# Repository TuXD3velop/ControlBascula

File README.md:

# ControlBascula
Controla el on-off de un motor que llena un recipiente, usando el peso de la bascula como parametro

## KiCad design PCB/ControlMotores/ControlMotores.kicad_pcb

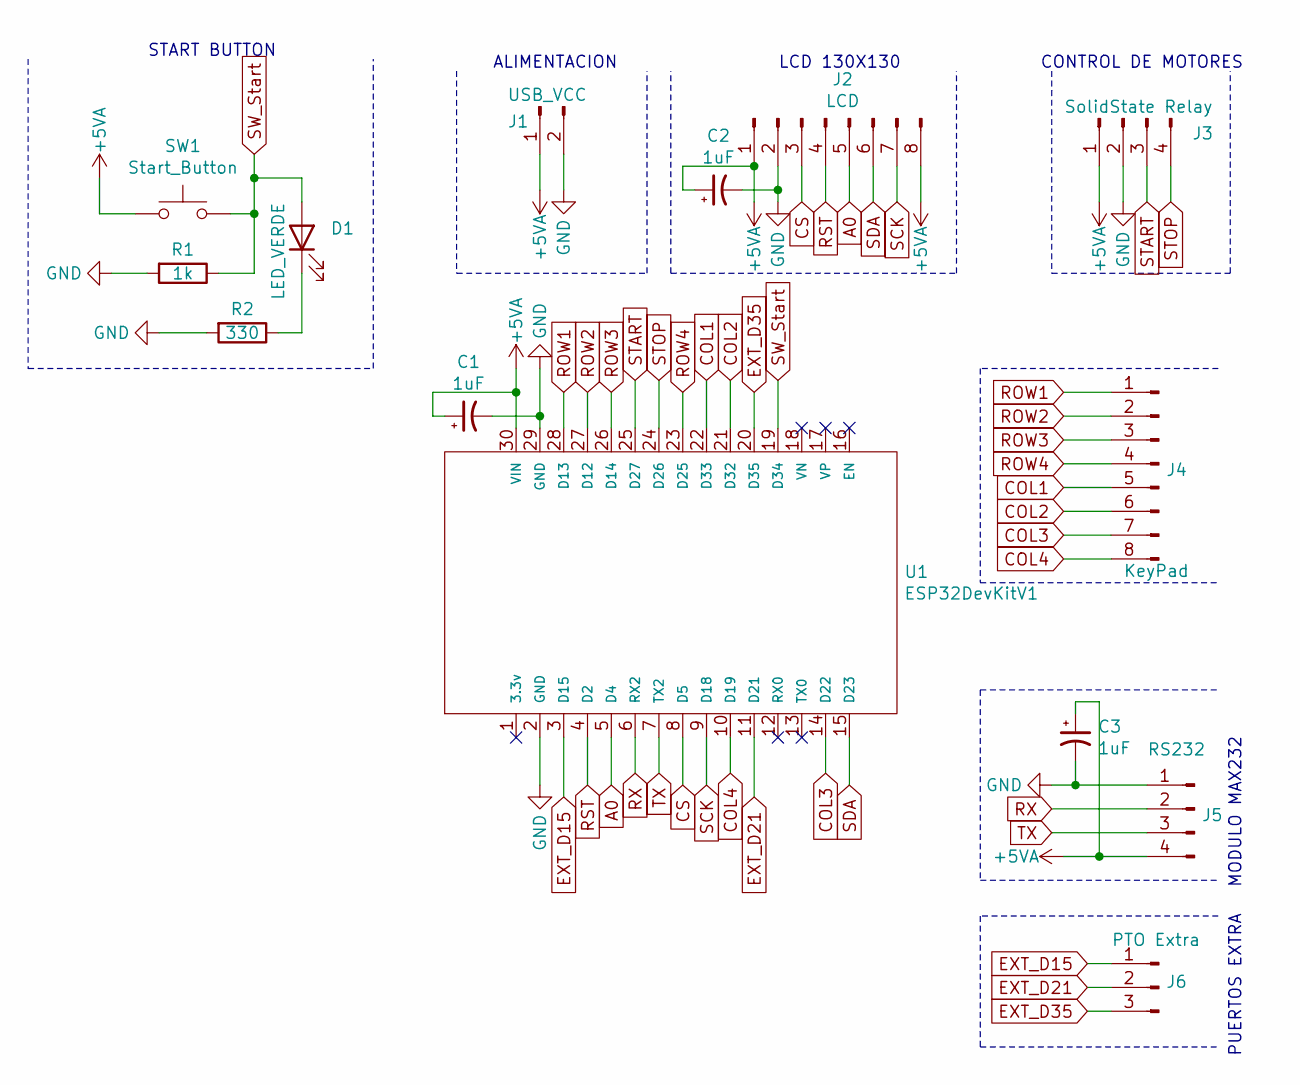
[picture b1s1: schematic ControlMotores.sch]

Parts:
C1, C2, C3: 1uF; CP_Radial_D8.0mm_P3.80mm
D1: LED_VERDE; PinHeader_1x02_P2.54mm_Vertical
J1: USB_VCC; PinHeader_1x02_P2.54mm_Horizontal
J2: LCD; PinHeader_1x08_P2.54mm_Vertical
J3: SolidState Relay; PinHeader_1x04_P2.54mm_Vertical
J4: KeyPad; PinHeader_1x08_P2.54mm_Vertical
J5: RS232; PinHeader_1x04_P2.54mm_Vertical
J6: PTO Extra; PinHeader_1x03_P2.54mm_Vertical
R1: 1k; R_Axial_DIN0204_L3.6mm_D1.6mm_P7.62mm_Horizontal
R2: 330; R_Axial_DIN0204_L3.6mm_D1.6mm_P7.62mm_Horizontal
SW1: Start_Button; TerminalBlock_bornier-2_P5.08mm
U1: ESP32DevKitV1

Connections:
+5VA: C1.1, C2.1, C3.1, J1.1, J2.1, J2.8, J3.1, J5.4, SW1.1, U1.30 (VIN)
A0: J2.5, U1.5 (D4)
COL1: J4.5, U1.22 (D33)
COL2: J4.6, U1.21 (D32)
COL3: J4.7, U1.14 (D22)
COL4: J4.8, U1.10 (D19)
CS: J2.3, U1.8 (D5)
EXT_D15: J6.1, U1.3 (D15)
EXT_D21: J6.2, U1.11 (D21)
EXT_D35: J6.3, U1.20 (D35)
GND: C1.2, C2.2, C3.2, J1.2, J2.2, J3.2, J5.1, R1.2, R2.2, U1.2 (GND), U1.29 (GND)
unnamed: D1.1 (K), R2.1
ROW1: J4.1, U1.28 (D13)
ROW2: J4.2, U1.27 (D12)
ROW3: J4.3, U1.26 (D14)
ROW4: J4.4, U1.23 (D25)
RST: J2.4, U1.4 (D2)
RX: J5.2, U1.6 (RX2)
SCK: J2.7, U1.9 (D18)
SDA: J2.6, U1.15 (D23)
START: J3.3, U1.25 (D27)
STOP: J3.4, U1.24 (D26)
SW_Start: D1.2 (A), R1.1, SW1.2, U1.19 (D34)
TX: J5.3, U1.7 (TX2)

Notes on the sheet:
ALIMENTACION
LCD 130X130
CONTROL DE MOTORES
MODULO MAX232
START BUTTON
PUERTOS EXTRA

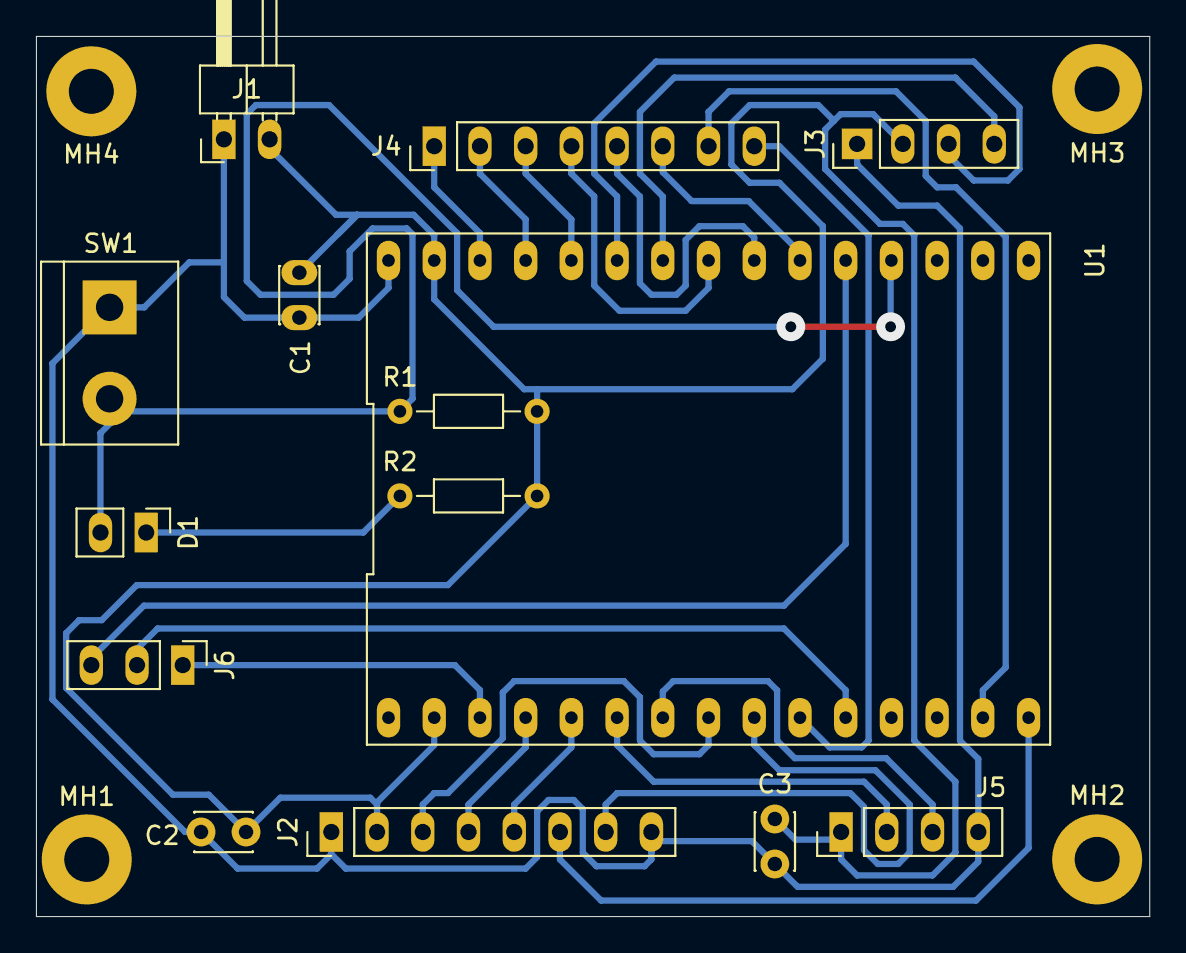
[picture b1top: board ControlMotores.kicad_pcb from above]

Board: 2 copper layers, 61.8 x 48.9 mm, 18 parts (0 on the bottom side), 24 nets.

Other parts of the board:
MH1: MH1; MountingHole_2.5mm_Pad
MH2: MH2; MountingHole_2.5mm_Pad
MH3: MH3; MountingHole_2.5mm_Pad
MH4: MH4; MountingHole_2.5mm_Pad

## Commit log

2023-03-07 Version 1 del programa, programa funcional inicio
2023-03-08 Cambio de los mensajes de depuracion en los enventos del teclado
2023-03-09 Arreglo temporal variable global del peso maximo
2023-03-09 Timeout de la coneccion wifi agregado
2023-03-09 Boton start y stop del keypad, funcionalidad agregada
2023-03-09 Agregado el retardo para el debounce del boton externo
2023-03-11 BugFix Eliminaciond el codigo dde preferencias
2023-03-11 Remueve la cabecera Preferences
2023-03-13 Archivos de kicad a nueva version 7.0
2023-03-14 Archivos de guardado de kicad
2023-03-14 Int externa eliminada, pulsador agregado en pin 34
2023-03-15 Sondeo del pin 34 sin interrupcion
2023-03-15 ISR Timer cada 100 ms, para sondeo de push button
2023-03-15 Cambio del Timer a 200ms
2023-03-16 Bug Fix, al inicio de programa se necnedia el motor
